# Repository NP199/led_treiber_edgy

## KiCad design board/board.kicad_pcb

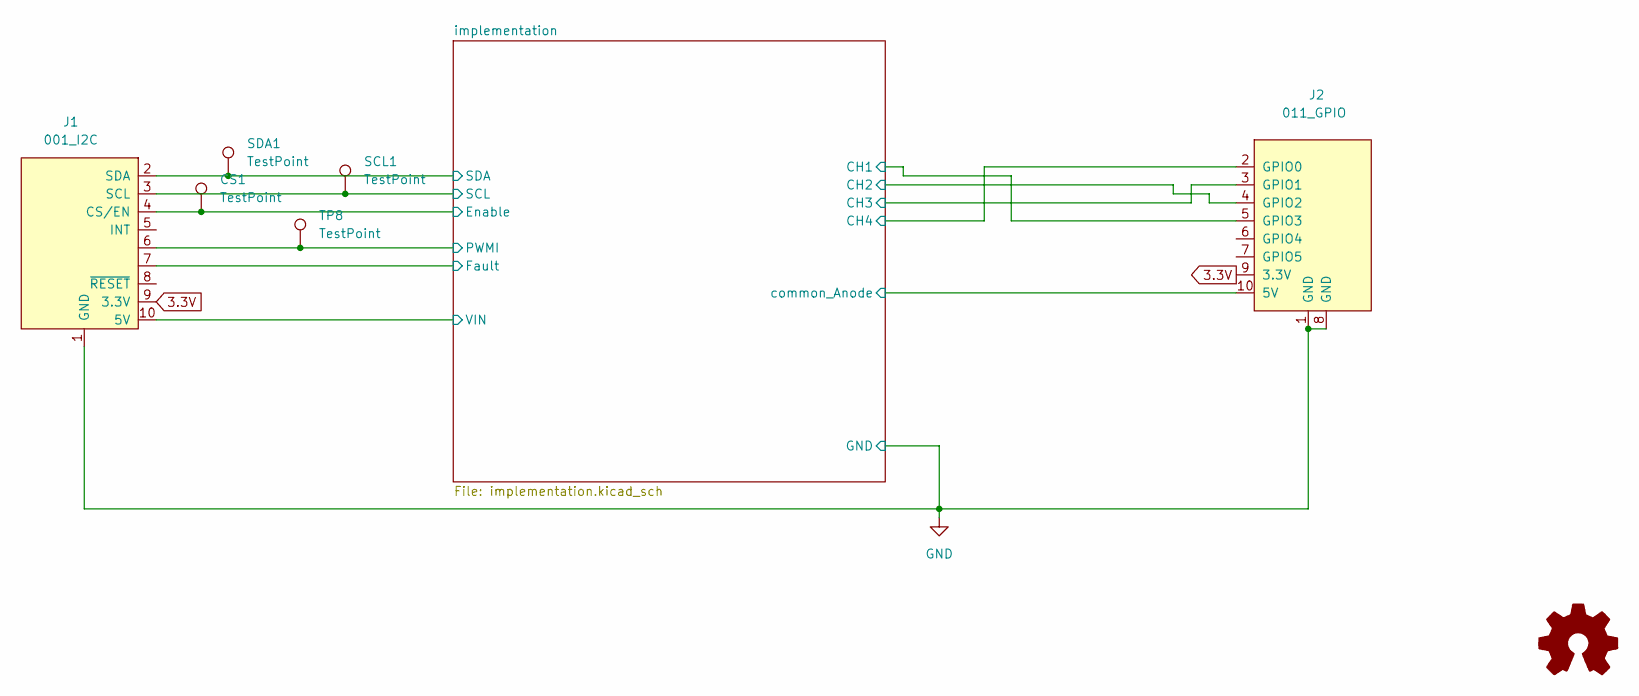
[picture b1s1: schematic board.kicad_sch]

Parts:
CS1: TestPoint; TestPoint_Pad_D1.0mm
J1: 001_I2C; on_edge_2x05_device
J2: 011_GPIO; on_edge_2x05_host
LOGO1: Logo_Open_Hardware_Small; OSHW-Symbol_6.7x6mm_SilkScreen
SCL1: TestPoint; TestPoint_Pad_D1.0mm
SDA1: TestPoint; TestPoint_Pad_D1.0mm
TP8: TestPoint; TestPoint_Pad_D1.0mm

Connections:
3.3V: J1.9 (3.3V), J2.9 (3.3V)
/implementation/CH1: J2.5 (GPIO3); also elsewhere on the board
/implementation/CH2: J2.4 (GPIO2); also elsewhere on the board
/implementation/CH3: J2.3 (GPIO1); also elsewhere on the board
/implementation/CH4: J2.2 (GPIO0); also elsewhere on the board
/implementation/Enable: CS1.1, J1.4 (CS/EN); also elsewhere on the board
/implementation/Fault: J1.7; also elsewhere on the board
/implementation/PWMI: J1.6; also elsewhere on the board
/implementation/SCL: J1.3 (SCL), SCL1.1; also elsewhere on the board
/implementation/SDA: J1.2 (SDA), SDA1.1; also elsewhere on the board
/implementation/VIN: J1.10 (5V); also elsewhere on the board
/implementation/common_Anode: J2.10 (5V); also elsewhere on the board
GND: J1.1 (GND), J2.1 (GND), J2.8 (GND); also elsewhere on the board

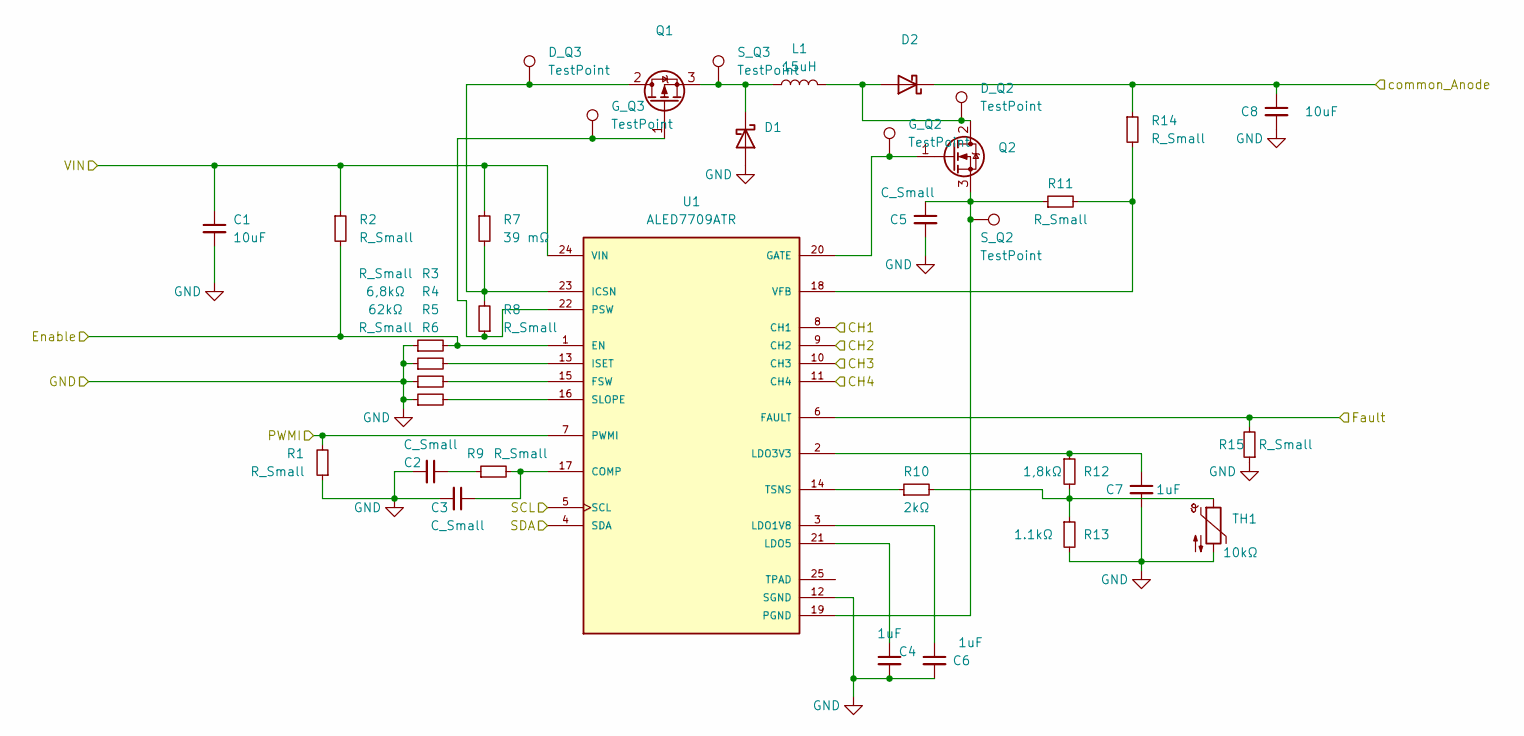
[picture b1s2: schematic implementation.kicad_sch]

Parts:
C1, C8: 10uF; C_0402_1005Metric
C2, C3, C5: C_Small; C_0402_1005Metric
C4, C6, C7: 1uF; C_0402_1005Metric
D1: D_SOD-123; MPN STPS1H100
D2: D_SMA; MPN STPS2L60AY
D_Q2, D_Q3: TestPoint; TestPoint_Pad_D1.0mm
G_Q2, G_Q3: TestPoint; TestPoint_Pad_D1.0mm
L1: 15uH; IND_XGL1010-332MED
Q1: TO-252-2; MPN SQD50P08-25L_GE3
Q2: TO-252-2; MPN MCU20N10-TP
R1, R2, R3, R6, R8, R9, R11, R14, R15: R_Small; R_0402_1005Metric
R4: 6,8kΩ; R_0402_1005Metric
R5: 62kΩ; R_0402_1005Metric
R7: 39 mΩ; R_0402_1005Metric
R10: 2kΩ; R_0402_1005Metric
R12: 1,8kΩ; R_0402_1005Metric
R13: 1.1kΩ; R_0402_1005Metric
S_Q2, S_Q3: TestPoint; TestPoint_Pad_D1.0mm
TH1: 10kΩ; R_0603_1608Metric; MPN NCG18XH103F0SRB
U1: ALED7709ATR; QFN65P500X500X90-25N; PARTREV 1

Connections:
/implementation/CH1: U1.8 (CH1); also elsewhere on the board
/implementation/CH2: U1.9 (CH2); also elsewhere on the board
/implementation/CH3: U1.10 (CH3); also elsewhere on the board
/implementation/CH4: U1.11 (CH4); also elsewhere on the board
/implementation/Enable: R2.2, R3.2, U1.1 (EN); also elsewhere on the board
/implementation/Fault: R15.2, U1.6 (FAULT); also elsewhere on the board
/implementation/PWMI: R1.2, U1.7 (PWMI); also elsewhere on the board
/implementation/SCL: U1.5 (SCL); also elsewhere on the board
/implementation/SDA: U1.4 (SDA); also elsewhere on the board
/implementation/VIN: C1.1, R2.1, R7.1, U1.24 (VIN); also elsewhere on the board
/implementation/common_Anode: C8.1, D2.1 (K), R14.1; also elsewhere on the board
GND: C1.2, C2.2, C3.2, C4.2, C5.2, C6.2, C7.2, C8.2, D1.2 (A), R1.1, R3.1, R4.1, R5.1, R6.1, R13.2, R15.1, TH1.2, U1.12 (SGND); also elsewhere on the board
unnamed: C2.1, R9.1
unnamed: D1.1 (K), L1.1, Q1.3 (S), S_Q3.1
unnamed: D2.2 (A), D_Q2.1, L1.2, Q2.2 (D)
unnamed: D_Q3.1, Q1.2 (D), R7.2, R8.2, U1.23 (ICSN)
unnamed: G_Q3.1, Q1.1 (G), R8.1, U1.22 (PSW)
unnamed: G_Q2.1, Q2.1 (G), U1.20 (GATE)
unnamed: C5.1, Q2.3 (S), R11.1, S_Q2.1, U1.19 (PGND)
unnamed: R10.2, R12.2, R13.1, TH1.1
unnamed: C3.1, R9.2, U1.17 (COMP)
unnamed: R5.2, U1.15 (FSW)
unnamed: R4.2, U1.13 (ISET)
unnamed: C6.1, U1.3 (LDO1V8)
unnamed: C7.1, R12.1, U1.2 (LDO3V3)
unnamed: C4.1, U1.21 (LDO5)
unnamed: R6.2, U1.16 (SLOPE)
unnamed: R10.1, U1.14 (TSNS)
unnamed: R11.2, R14.2, U1.18 (VFB)

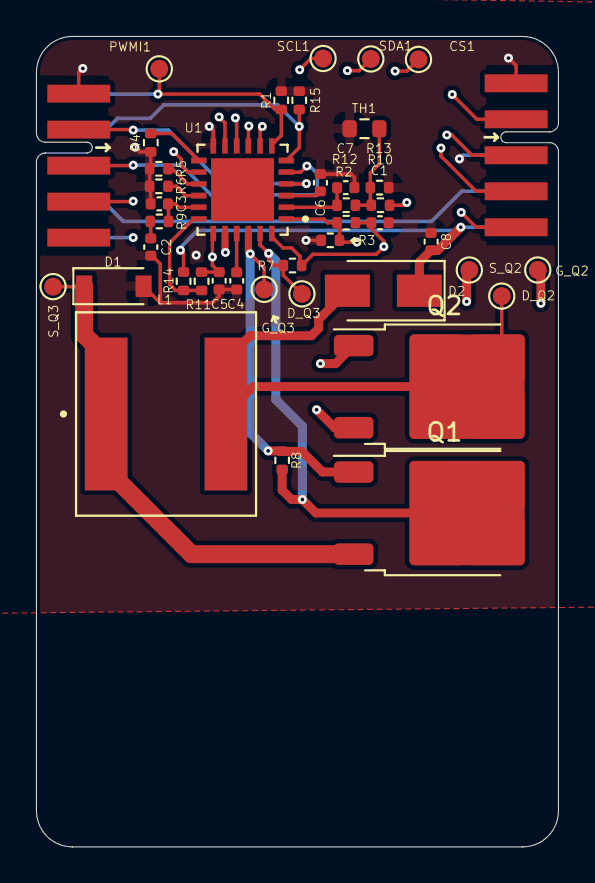
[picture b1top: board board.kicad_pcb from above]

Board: 4 copper layers, 29.0 x 45.0 mm, 43 parts (1 on the bottom side), 30 nets.

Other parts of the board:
PWMI1: TestPoint; TestPoint_Pad_D1.0mm

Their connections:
/implementation/PWMI: PWMI1.1; also elsewhere on the board

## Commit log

2023-05-28 Add footprint, schema, 3D Model | Start circuit design
2023-05-28 Add footprint, symbol and 3D modell | Add parts for reference cicuit
2023-06-05 Add routing
2023-06-06 Add Testpoint | Add relative footrpint/symbol path
2023-06-08 Update PCB
2023-10-23 Update design
2023-10-31 Update footprint for MOSFETS
